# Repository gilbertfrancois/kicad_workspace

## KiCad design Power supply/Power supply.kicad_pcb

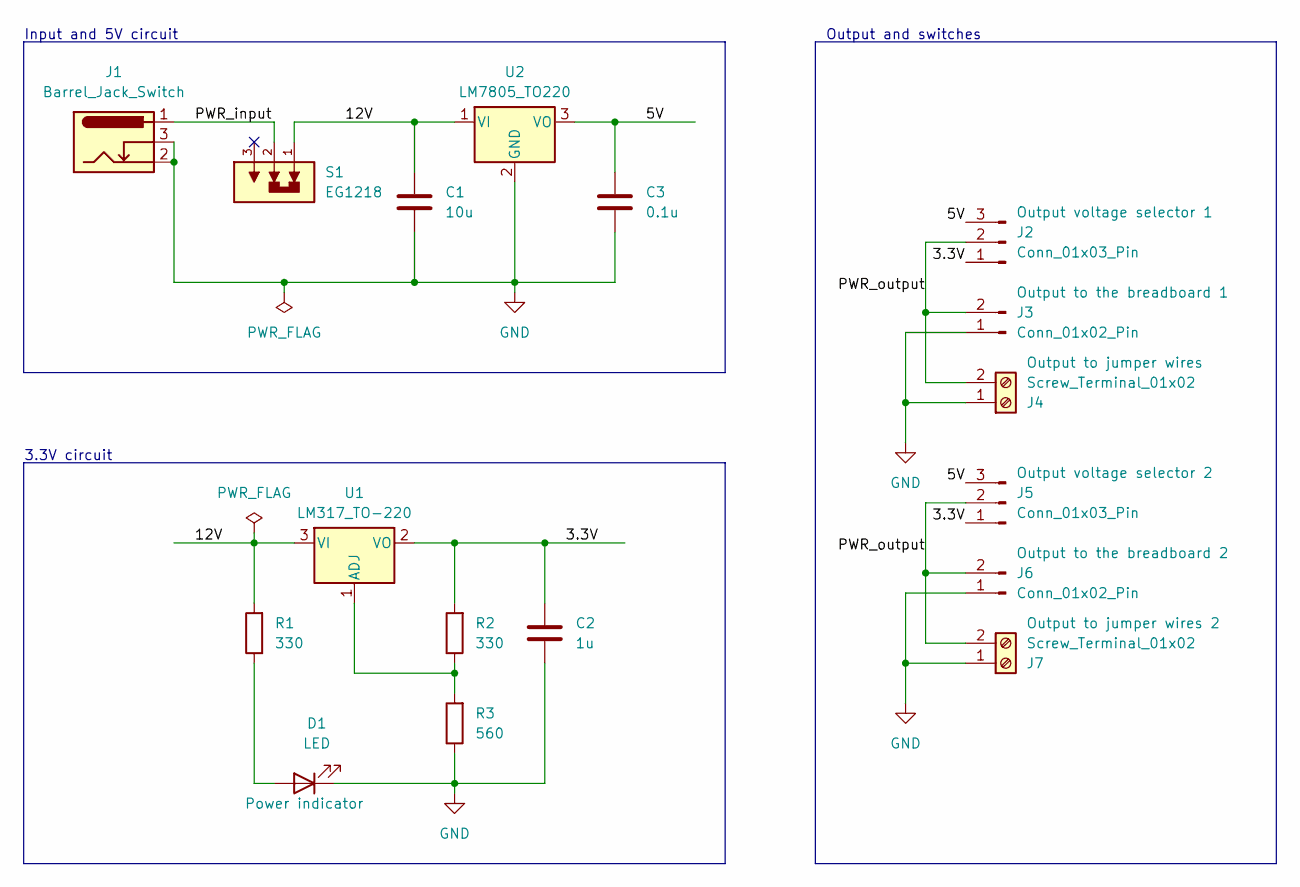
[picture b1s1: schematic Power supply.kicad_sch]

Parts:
C1: 10u; C_Disc_D3.0mm_W1.6mm_P2.50mm
C2: 1u; C_Disc_D3.0mm_W1.6mm_P2.50mm
C3: 0.1u; C_Disc_D3.0mm_W1.6mm_P2.50mm
D1: LED; LED_D5.0mm
J1: Barrel_Jack_Switch; BarrelJack_Horizontal
J2, J5: Conn_01x03_Pin; PinHeader_1x03_P2.54mm_Vertical
J3, J6: Conn_01x02_Pin; PinHeader_1x02_P2.54mm_Vertical
J4, J7: Screw_Terminal_01x02; TerminalBlock_bornier-2_P5.08mm
R1, R2: 330; R_Axial_DIN0204_L3.6mm_D1.6mm_P7.62mm_Horizontal
R3: 560; R_Axial_DIN0204_L3.6mm_D1.6mm_P7.62mm_Horizontal
S1: EG1218; Switch_Slide_11.6x4mm_EG1218
U1: LM317_TO-220; TO-220-3_Vertical
U2: LM7805_TO220; TO-220-3_Vertical

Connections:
/3.3V: C2.1, J2.1, J5.1, R2.2, U1.2 (VO)
/5V: C3.1, J2.3, J5.3, U2.3 (VO)
/12V: C1.1, R1.2, S1.1, U1.3 (VI), U2.1 (VI)
/PWR_input: J1.1, S1.2
/PWR_output: J2.2, J3.2, J4.2, J5.2, J6.2, J7.2
GND: C1.2, C2.2, C3.2, D1.1 (K), J1.2, J1.3, J3.1, J4.1, J6.1, J7.1, R3.1, U2.2 (GND)
unnamed: D1.2 (A), R1.1
unnamed: R2.1, R3.2, U1.1 (ADJ)

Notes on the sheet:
3.3V circuit
Output and switches
Input and 5V circuit

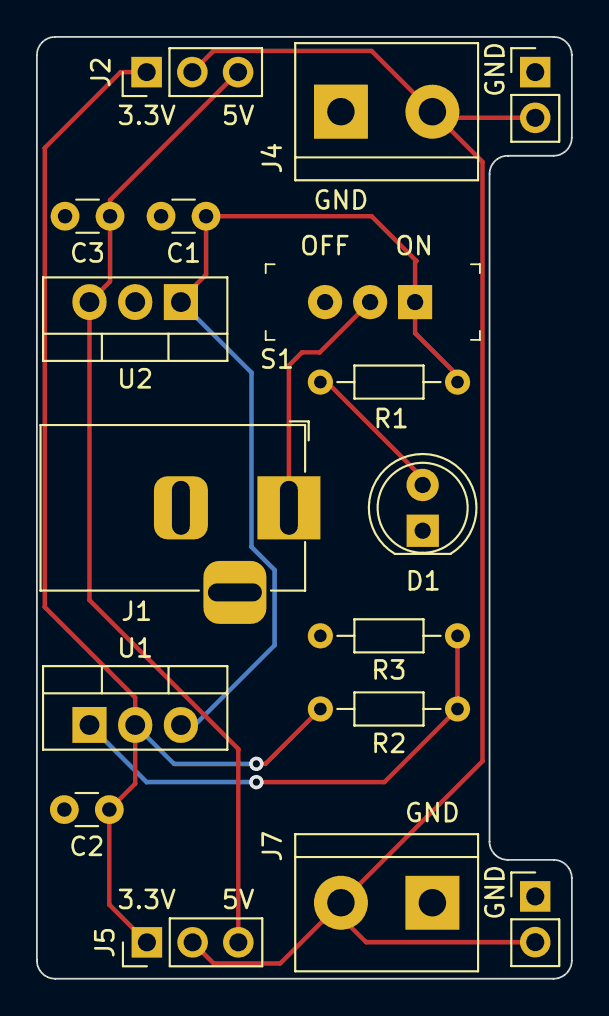
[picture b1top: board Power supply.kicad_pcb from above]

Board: 2 copper layers, 29.7 x 52.3 mm, 17 parts (0 on the bottom side), 8 nets.

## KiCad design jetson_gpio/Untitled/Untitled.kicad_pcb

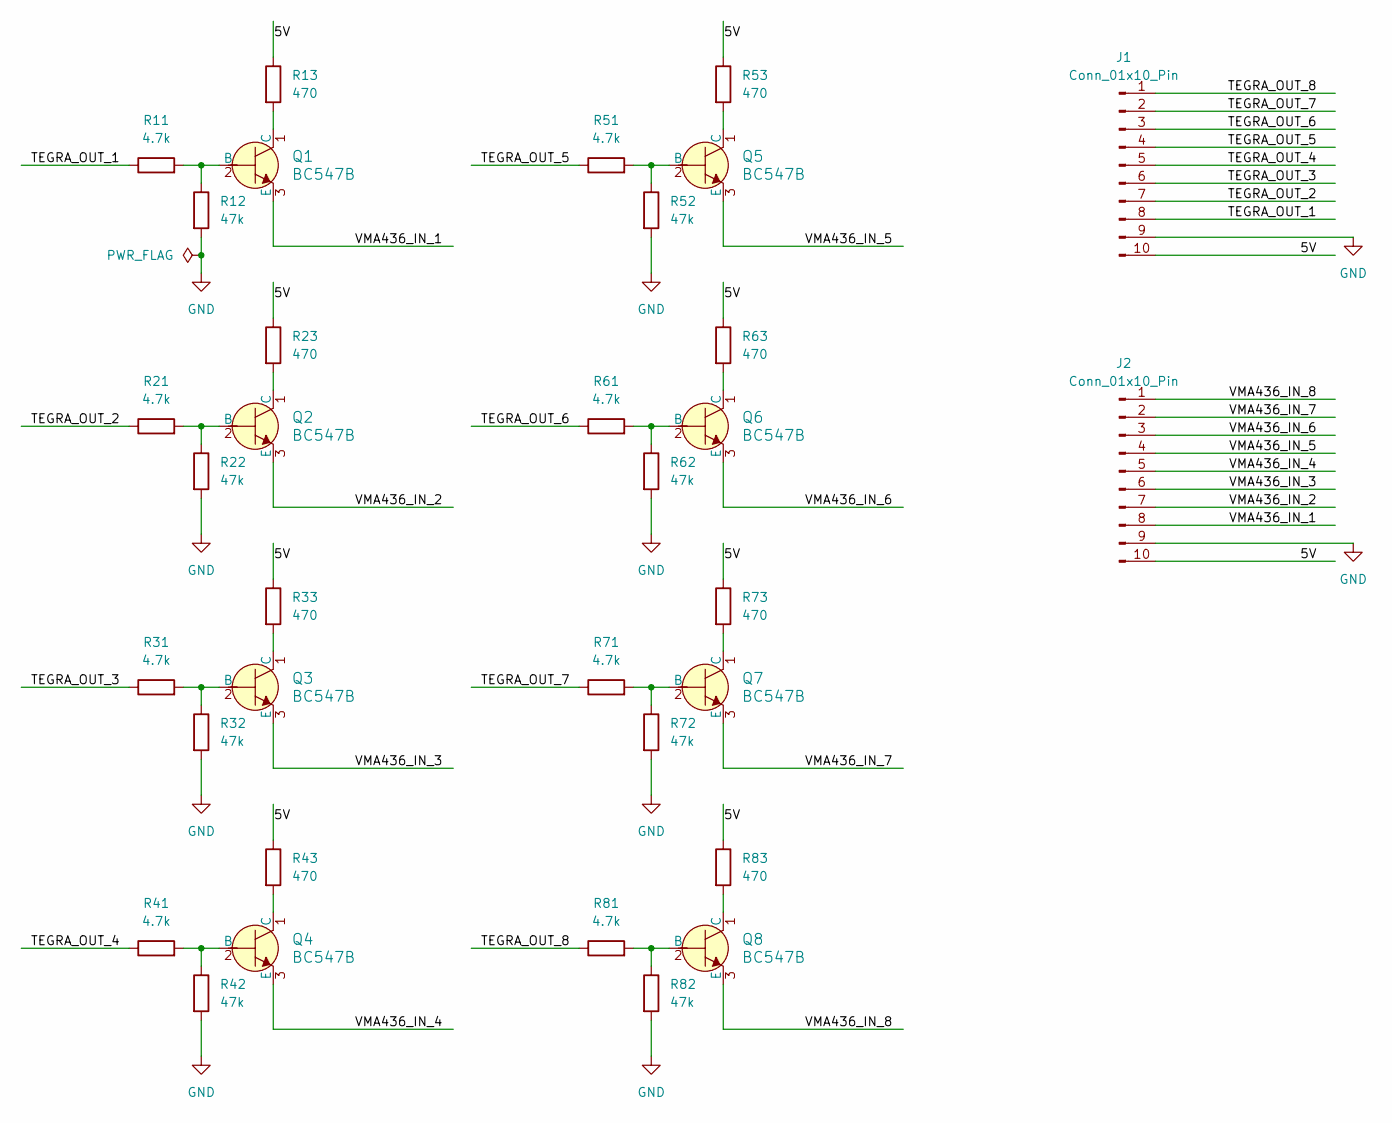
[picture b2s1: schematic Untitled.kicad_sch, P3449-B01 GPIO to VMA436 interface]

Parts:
J1, J2: Conn_01x10_Pin; PinHeader_1x10_P2.54mm_Vertical
Q1, Q2, Q3, Q4, Q5, Q6, Q7, Q8: BC547B; TO-92-3_Formed_Leads; MPN BC547BTA; Digi-Key_PN BC547BTACT-ND
R11, R21, R31, R41, R51, R61, R71, R81: 4.7k; R_Axial_DIN0204_L3.6mm_D1.6mm_P7.62mm_Horizontal
R12, R22, R32, R42, R52, R62, R72, R82: 47k; R_Axial_DIN0204_L3.6mm_D1.6mm_P7.62mm_Horizontal
R13, R23, R33, R43, R53, R63, R73, R83: 470; R_Axial_DIN0204_L3.6mm_D1.6mm_P7.62mm_Horizontal

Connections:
/5V: J1.10, J2.10, R13.1, R23.1, R33.1, R43.1, R53.1, R63.1, R73.1, R83.1
/TEGRA_OUT_1: J1.8, R11.1
/TEGRA_OUT_2: J1.7, R21.1
/TEGRA_OUT_3: J1.6, R31.1
/TEGRA_OUT_4: J1.5, R41.1
/TEGRA_OUT_5: J1.4, R51.1
/TEGRA_OUT_6: J1.3, R61.1
/TEGRA_OUT_7: J1.2, R71.1
/TEGRA_OUT_8: J1.1, R81.1
/VMA436_IN_1: J2.8, Q1.3 (E)
/VMA436_IN_2: J2.7, Q2.3 (E)
/VMA436_IN_3: J2.6, Q3.3 (E)
/VMA436_IN_4: J2.5, Q4.3 (E)
/VMA436_IN_5: J2.4, Q5.3 (E)
/VMA436_IN_6: J2.3, Q6.3 (E)
/VMA436_IN_7: J2.2, Q7.3 (E)
/VMA436_IN_8: J2.1, Q8.3 (E)
GND: J1.9, J2.9, R12.2, R22.2, R32.2, R42.2, R52.2, R62.2, R72.2, R82.2
unnamed: Q1.2 (B), R11.2, R12.1
unnamed: Q1.1 (C), R13.2
unnamed: Q2.2 (B), R21.2, R22.1
unnamed: Q2.1 (C), R23.2
unnamed: Q3.2 (B), R31.2, R32.1
unnamed: Q3.1 (C), R33.2
unnamed: Q4.2 (B), R41.2, R42.1
unnamed: Q4.1 (C), R43.2
unnamed: Q5.2 (B), R51.2, R52.1
unnamed: Q5.1 (C), R53.2
unnamed: Q6.2 (B), R61.2, R62.1
unnamed: Q6.1 (C), R63.2
unnamed: Q7.2 (B), R71.2, R72.1
unnamed: Q7.1 (C), R73.2
unnamed: Q8.2 (B), R81.2, R82.1
unnamed: Q8.1 (C), R83.2

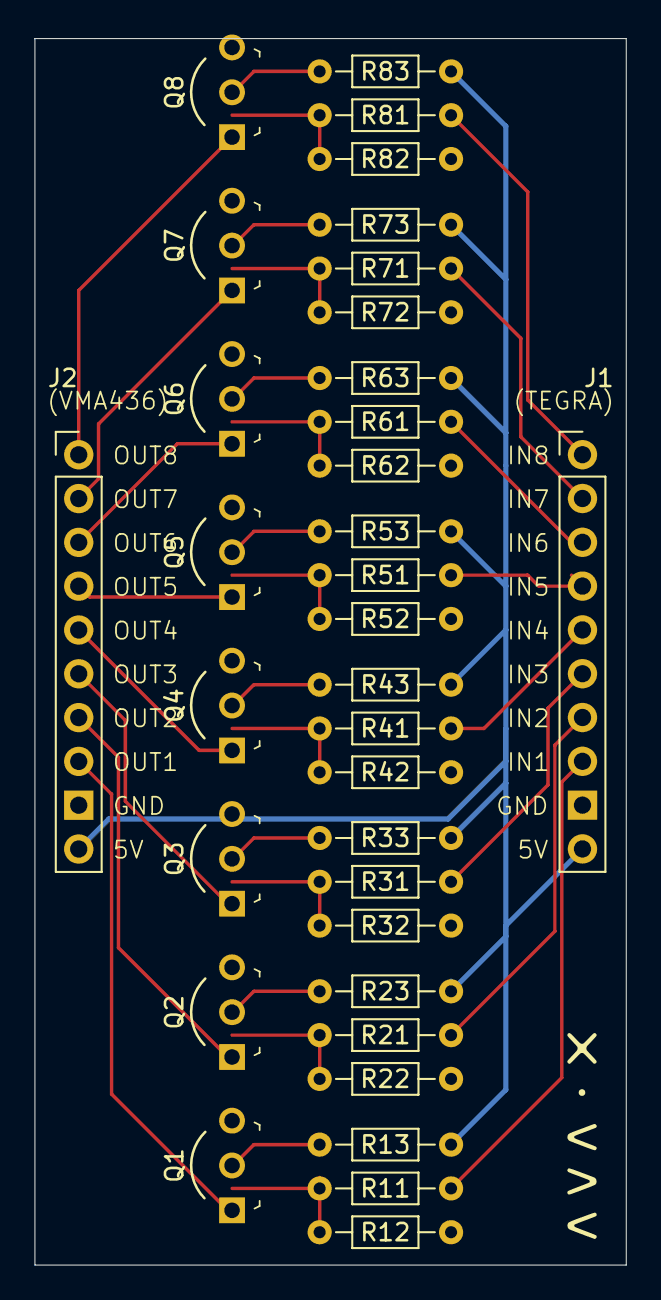
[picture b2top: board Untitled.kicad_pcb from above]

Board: 2 copper layers, 34.3 x 71.1 mm, 34 parts (0 on the bottom side), 34 nets.
